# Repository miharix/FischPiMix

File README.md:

https://www.youtube.com/watch?v=leHwTYAQO-k

https://www.youtube.com/watch?v=ODTY9RQhn2A

DE:
Den FishPiMix Modul habe ich entwickelt um in meiner Grundschule besser die Grundlagen der Robotik zu unterrichten. Momentan habe ich keine plane den FishPiMix zu produzieren, aber wen du meinst der FishPiMix ist etwas was du eventuell kaufen mochtest, schick mir eine PM und vielleicht ändere ich meine Meinung und produziere kleine Serie zum verkaufen.

Technische Daten:
* bis 4 Ft. Motoren in beide Richtungen oder bis 8 andere Verbraucher (Licht, El. Magnet,..) max 1A
* 9 Ein/Aus Schalter
+ Sicherungen gegen Überlastung
+ RsPi Ausgang Sicherung (wen man den Eingang als Ausgang betreibt)
+ Sicherung gegen falschen Batterie Polarität
+ Entprellung der Schalter 

ENG:
I made the FishPiMix module to better teach robotic in my primary class. At this moment I have no plans to making a FishPiMix for seling. But If you thing, FishPiMix is something you would like to buy, let me know. Maybe I'll change my mind and make a small quantity for selling. 

Technical data:
* max 4 Ft. motors individual controllable in both directions
* max 9 On/Off switches
+ fuses against overloading
+ RsPi GPIO protection against wrong direction (using an input as output)
+ Battery polarity protection
+ Button denounce circuit

SLO:
FishPiMix sem razvil za potrebe izbirnega predmeta v OŠ - Robotika v tehniki. Zaenkrat ne planiram prodajat module a če si učitelj(ca) in te zanima več o tem modulu mi piši, če vas bo več si mogoče premislim pa naredimo kako brezplačno delavnico. ;)

Tehnični podatki:
* 4 krtačnih motorčkov v obe smeri in z poljubno hitrostjo max 1A na motor
ali do 8 naprav npr žarnica, piskač... (vse iz FT kompletov) kjer lahko za vsako posebaj krmiliš napetost (PWM signal)
 * 9 on/off vhodov npr stikala, tipke, foto tranzistor (vse iz FT kompletov)
+ avtomatcke varovalke ob preobrementivi izhodov,
+ začito RPi če pomotoma nastaviš priključek on/off kot izhod in je stikalo sklenjeno (da ne skuriš RPi)
+ zaščito pred napačno prikločitvijo baterije za napajanje motorčkov (do 24V)
+ sistem za glajenje nečistih signalov zaradi uporabe slabih stikal (iskrenje)
+ vezje preprosto natakneš na RPi in dela

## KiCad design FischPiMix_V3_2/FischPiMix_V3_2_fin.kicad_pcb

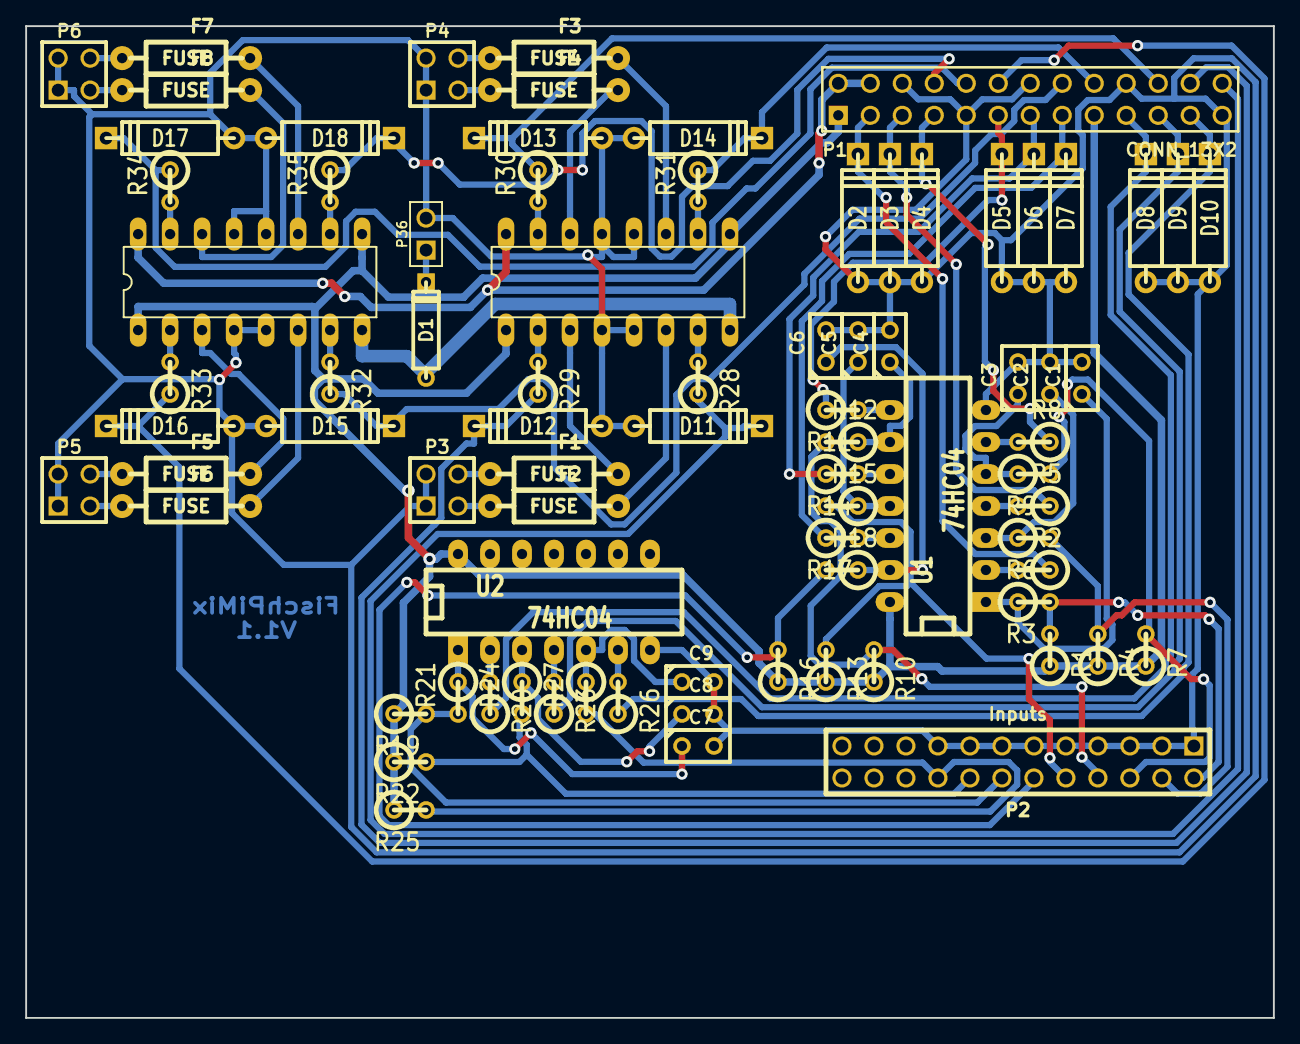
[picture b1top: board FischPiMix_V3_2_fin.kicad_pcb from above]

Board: 2 copper layers, 99.1 x 78.7 mm, 81 parts (0 on the bottom side), 73 nets.

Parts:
C1, C2, C3, C4, C5, C6, C7, C8, C9: 1uF; C1
D1: DIODE; D3
D2, D3, D4, D5, D6, D7, D8, D9, D10, D11, D12, D13, D14, D15, D16, D17, D18: 3,3V; D4
F1, F2, F3, F4, F5, F6, F7, F8: FUSE; R250-4
IC1, IC2: SN754410; HBridge-DIP16
P1: CONN_13X2; pin_array_13x2
P2: Inputs; pin_array_12x2
P3: Motor1; PIN_ARRAY_2X2
P4: Motor2; PIN_ARRAY_2X2
P5: Motor3; PIN_ARRAY_2X2
P6: Motor4; PIN_ARRAY_2X2
P36: Bat9V; PIN_ARRAY_2X1
R1, R2, R4, R5, R7, R8, R10, R11, R13, R14, R16, R17, R19, R20, R22, R23, R25, R26, R28, R29, R30, R31, R32, R33, R34, R35: 330; R1
R3, R6, R9, R12, R15, R18, R21, R24, R27: 1k; R1
U1, U2: 74HC04; DIP-14__300_ELL

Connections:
+3.3V: IC1.1, IC1.9, IC2.1, IC2.9, P1.1, P1.17, R1.1, R4.1, R7.1, R10.1, R13.1, R16.1, R19.1, R22.1, R25.1, U1.14, U2.14
+5V: IC1.16, IC2.16, P1.2, P1.4
+9V: D1.1, IC1.8, IC2.8
/GPIO0(SDA): D2.2, P1.3, R2.1
/GPIO1(SCL): D3.2, P1.5, R5.1
/GPIO4: D4.2, P1.7, R8.1
/GPIO9(MISO): D9.2, P1.21, R23.1
/GPIO10(MOSI): D8.2, P1.19, R20.1
/GPIO11(SCLK): D10.2, P1.23, R26.1
/GPIO17: D5.2, P1.11, R11.1
/GPIO18: D16.2, P1.12, R33.1
/GPIO21: D6.2, P1.13, R14.1
/GPIO22: D7.2, P1.15, R17.1
/GPIO23: D15.2, P1.16, R32.1
/GPIO24: D14.2, P1.18, R31.1
/GPIO25: D13.2, P1.22, R30.1
/RXD: D17.2, P1.10, R34.1
/TXD: D18.2, P1.8, R35.1
GND: C1.2, C2.2, C3.2, C4.2, C5.2, C6.2, C7.2, C8.2, C9.2, D2.1, D3.1, D4.1, D5.1, D6.1, D7.1, D8.1, D9.1, D10.1, D11.1, D12.1, D13.1, D14.1, D15.1, D16.1, D17.1, D18.1, IC1.4, IC1.5, IC1.12, IC1.13, IC2.4, IC2.5, IC2.12, IC2.13, P1.6, P1.9, P1.14, P1.20, P1.25, P2.1, P2.3, P2.5, P2.7, P2.9, P2.11, P2.13, P2.15, P2.17, P3.1, P3.2, P4.1, P4.2, P5.1, P5.2, P6.1, P6.2, P36.2, U1.7, U2.7
unnamed: P2.8, R10.2, R12.2
unnamed: R11.2, U1.8
unnamed: C5.1, R15.1, U1.11
unnamed: P2.10, R13.2, R15.2
unnamed: R14.2, U1.10
unnamed: C3.1, R9.1, U1.5
unnamed: P2.6, R7.2, R9.2
unnamed: R8.2, U1.6
unnamed: C4.1, R12.1, U1.9
unnamed: P2.14, R19.2, R21.2
unnamed: R20.2, U2.2
unnamed: C8.1, R24.1, U2.3
unnamed: P2.16, R22.2, R24.2
unnamed: R23.2, U2.4
unnamed: C6.1, R18.1, U1.13
unnamed: P2.12, R16.2, R18.2
unnamed: R17.2, U1.12
unnamed: C7.1, R21.1, U2.1
unnamed: F6.1, P5.3
unnamed: F5.1, P5.4
unnamed: C2.1, R6.1, U1.3
unnamed: P2.2, R1.2, R3.2
unnamed: R2.2, U1.2
unnamed: P2.4, R4.2, R6.2
unnamed: R5.2, U1.4
unnamed: D1.2, P36.1
unnamed: C1.1, R3.1, U1.1
unnamed: IC2.10, R35.2
unnamed: IC2.2, R33.2
unnamed: IC2.7, R32.2
unnamed: IC2.15, R34.2
unnamed: F6.2, IC2.6
unnamed: F5.2, IC2.3
unnamed: F7.2, IC2.11
unnamed: F8.2, IC2.14
unnamed: F1.1, P3.4
unnamed: IC1.2, R29.2
unnamed: IC1.7, R28.2
unnamed: IC1.15, R30.2
unnamed: IC1.10, R31.2
unnamed: F2.2, IC1.6
unnamed: F1.2, IC1.3
unnamed: F3.2, IC1.11
unnamed: F4.2, IC1.14
unnamed: F2.1, P3.3
unnamed: F3.1, P4.4
unnamed: F4.1, P4.3
unnamed: F7.1, P6.4
unnamed: F8.1, P6.3
unnamed: P2.18, R25.2, R27.2
unnamed: C9.1, R27.1, U2.5
unnamed: R26.2, U2.6
unnamed: D12.2, P1.24, R29.1
unnamed: D11.2, P1.26, R28.1

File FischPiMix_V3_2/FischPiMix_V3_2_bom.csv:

1uF;9;"C1 C2 C3 C4 C5 C6 C7 C8 C9"
3,3V;17;"D2 D3 D4 D5 D6 D7 D8 D9 D10 D11 D12 D13 D14 D15 D16 D17 D18"
DIODE;1;"D1"
FUSE;8;"F1 F2 F3 F4 F5 F6 F7 F8"
SN754410;2;"IC1 IC2"
CONN_13X2;1;"P1"
CONNECTOR;18;"P2 P7 P8 P9 P10 P11 P12 P13 P14 P15 P16 P17 P18 P19 P20 P21 P22 P23"
Motor1;1;"P3"
Motor2;1;"P4"
Motor3;1;"P5"
Motor4;1;"P6"
Bat9V;1;"P36"
330;26;"R1 R2 R4 R5 R7 R8 R10 R11 R13 R14 R16 R17 R19 R20 R22 R23 R25 R26 R28 R29 R30 R31 R32 R33 R34 R35"
1k;9;"R3 R6 R9 R12 R15 R18 R21 R24 R27"
74HC04;2;"U1 U2"

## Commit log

2014-09-17 Opis projekta
2014-09-17 V3_2
